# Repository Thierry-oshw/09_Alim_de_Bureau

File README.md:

# 09_Alim_de_Bureau
 Alimentation de bureau à partir d'une alim de pc

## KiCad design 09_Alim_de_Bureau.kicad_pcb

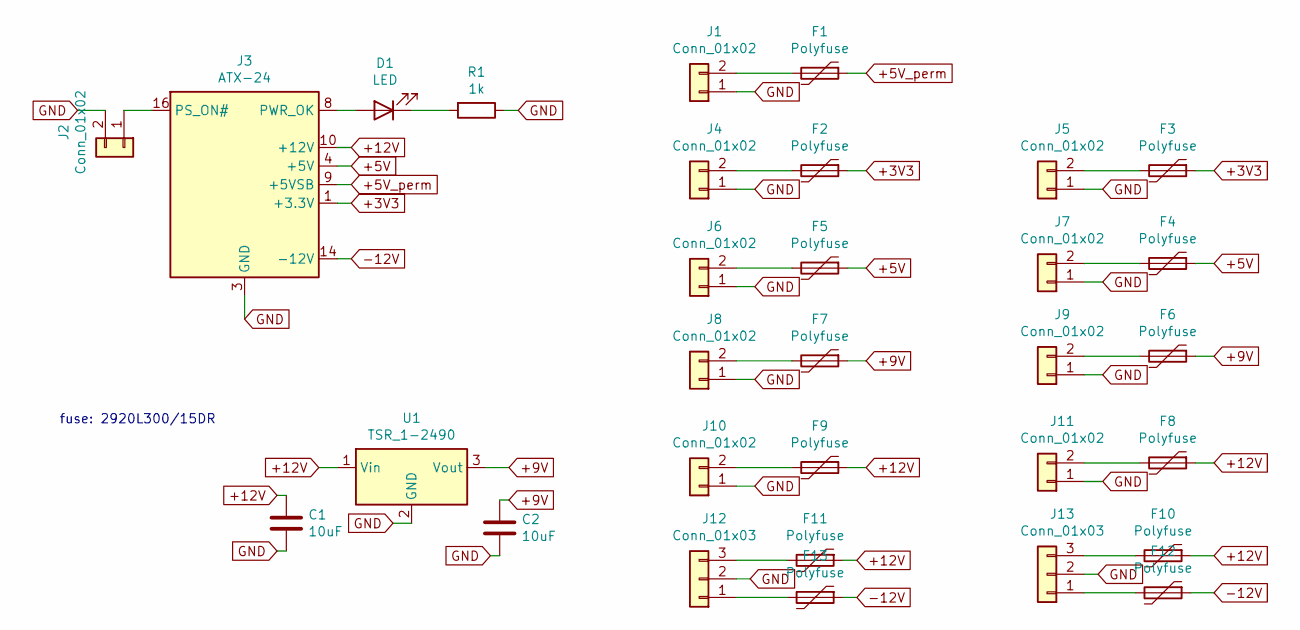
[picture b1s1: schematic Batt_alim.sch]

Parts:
C1, C2: 10uF; CP_Radial_D8.0mm_P3.80mm
D1: LED; LED_D4.0mm
F1, F2, F3, F4, F5, F6, F7, F8, F9, F10, F11, F12, F13: Polyfuse; Fuse_2920_7451Metric_Pad2.10x5.45mm_HandSolder
J1, J2, J4, J5, J6, J7, J8, J9, J10, J11: Conn_01x02; JST_XH_B2B-XH-A_1x02_P2.50mm_Vertical
J3: ATX-24; Molex_Mini-Fit_Jr_5566-24A_2x12_P4.20mm_Vertical
J12, J13: Conn_01x03; JST_XH_B3B-XH-A_1x03_P2.50mm_Vertical
R1: 1k; R_0603_1608Metric_Pad1.05x0.95mm_HandSolder
U1: TSR_1-2490; Converter_DCDC_TRACO_TSR-1_THT

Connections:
+3V3: F2.1, F3.1, J3.1 (+3.3V), J3.2 (+3.3V), J3.12 (+3.3V), J3.13 (+3.3V)
+5V: F4.1, F5.1, J3.4 (+5V), J3.6 (+5V), J3.21 (+5V), J3.22 (+5V), J3.23 (+5V)
+5V_perm: F1.1, J3.9 (+5VSB)
+9V: C2.1, F6.1, F7.1, U1.3 (Vout)
+12V: C1.1, F8.1, F9.1, F10.1, F11.1, J3.10 (+12V), J3.11 (+12V), U1.1 (Vin)
-12V: F12.1, F13.1, J3.14 (-12V)
GND: C1.2, C2.2, J1.1, J2.2, J3.3 (GND), J3.5 (GND), J3.7 (GND), J3.15 (GND), J3.17 (GND), J3.18 (GND), J3.19 (GND), J3.24 (GND), J4.1, J5.1, J6.1, J7.1, J8.1, J9.1, J10.1, J11.1, J12.2, J13.2, R1.1, U1.2 (GND); also elsewhere on the board
unnamed: D1.1 (K), R1.2
unnamed: D1.2 (A), J3.8 (PWR_OK)
unnamed: F1.2, J1.2
unnamed: F2.2, J4.2
unnamed: F3.2, J5.2
unnamed: F4.2, J7.2
unnamed: F5.2, J6.2
unnamed: F6.2, J9.2
unnamed: F7.2, J8.2
unnamed: F8.2, J11.2
unnamed: F9.2, J10.2
unnamed: F10.2, J13.3
unnamed: F11.2, J12.3
unnamed: F12.2, J13.1
unnamed: F13.2, J12.1
unnamed: J2.1, J3.16 (PS_ON#)

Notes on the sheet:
fuse: 2920L300/15DR

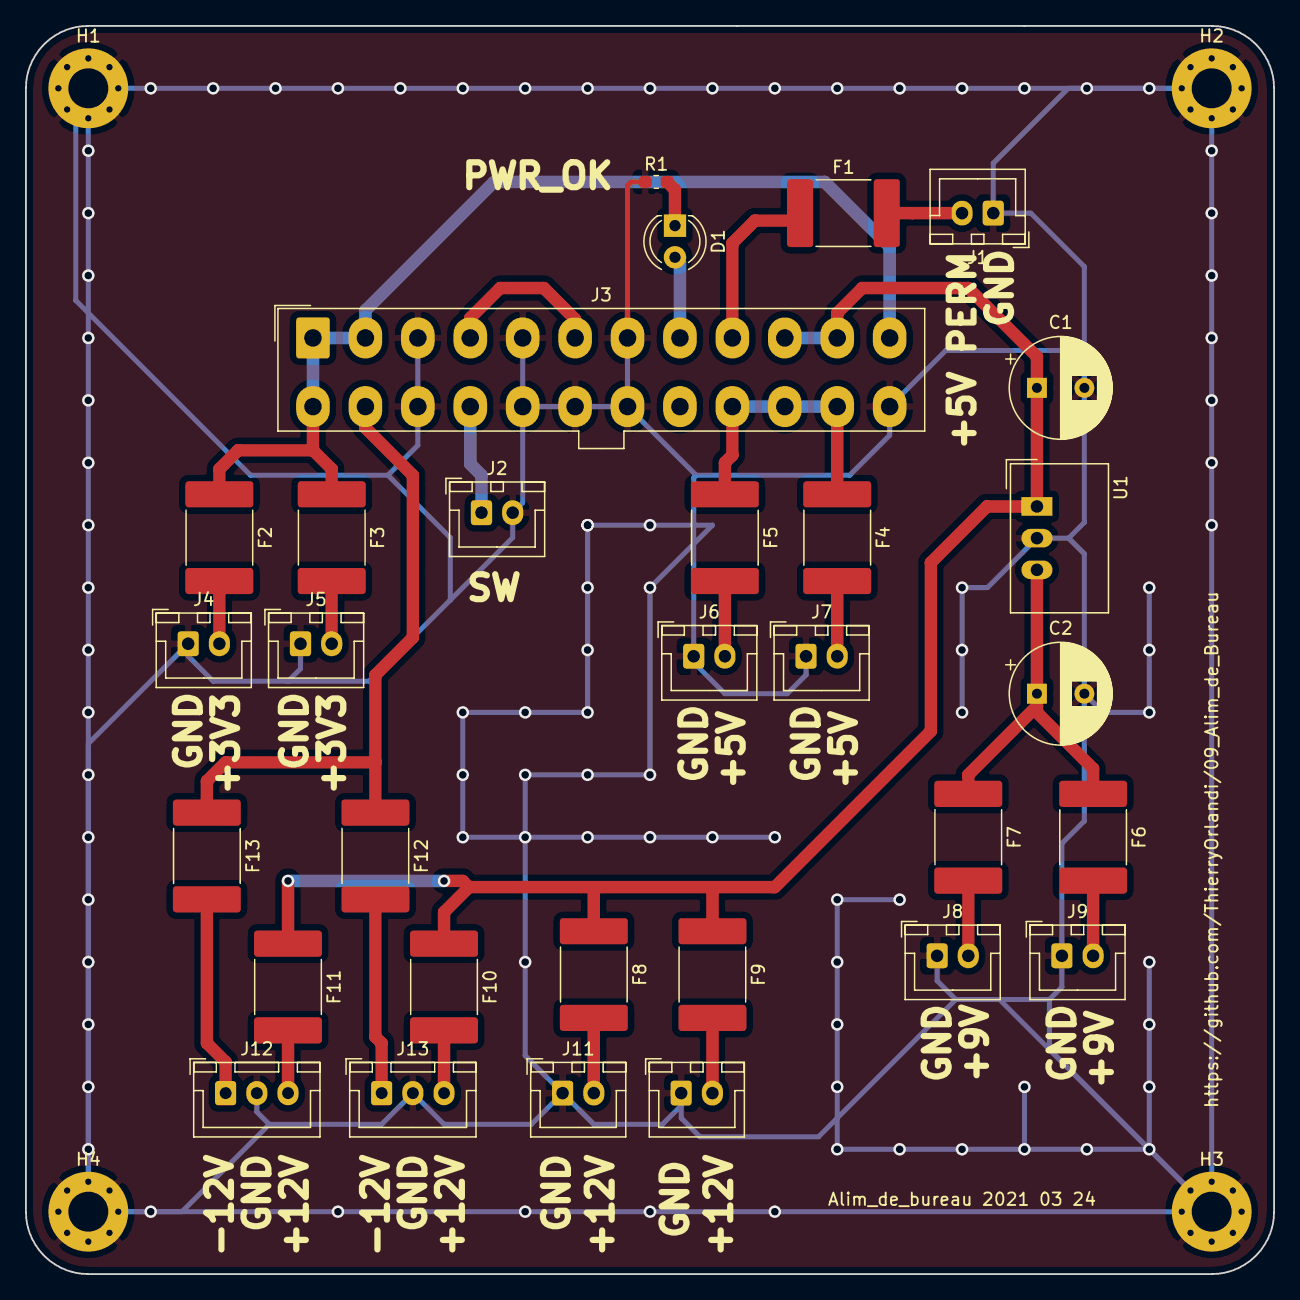
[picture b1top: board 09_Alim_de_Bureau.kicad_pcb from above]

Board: 2 copper layers, 100.0 x 100.0 mm, 35 parts (0 on the bottom side), 23 nets.

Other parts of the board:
H1, H2, H3, H4: MountingHole_Pad; MountingHole_3.2mm_M3_Pad_Via

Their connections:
GND: H1.1, H2.1, H3.1, H4.1; also elsewhere on the board

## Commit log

2021-03-24 initialisation
2021-07-24 maj split librairies
2023-05-02 chgt nom fichier licence
